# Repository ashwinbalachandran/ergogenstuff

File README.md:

# Summary

Just a repo to save any files related to the ergogen based keyboard I'm trying to build off of https://github.com/tapioki/cephalopoda/tree/main/Architeuthis%20dux

## Notes
The `adux_mod.yml` is not the exact yml that's in the image below, cause of the changes I made in Kicad.

## Changes from the original A.dux
- Changed footprint to `mx`
- Changed the spread and stagger for some columns
- Increased the size of the `raw` outline
- In Kicad
    - repositioned the `promicro` & `trrs` a little bit
    - randomly moved the "empty circles" to edges of the pcb
    - slightly changed the edges of the pcb

## Update - Final
Changes in https://github.com/ashwinbalachandran/ergogenstuff/pull/3

## Issues fixed
https://github.com/ashwinbalachandran/ergogenstuff/issues/1

## Images
Fixed all errors & warning thanks to @duckyb
### Final state

### Broken state - Pre fix?

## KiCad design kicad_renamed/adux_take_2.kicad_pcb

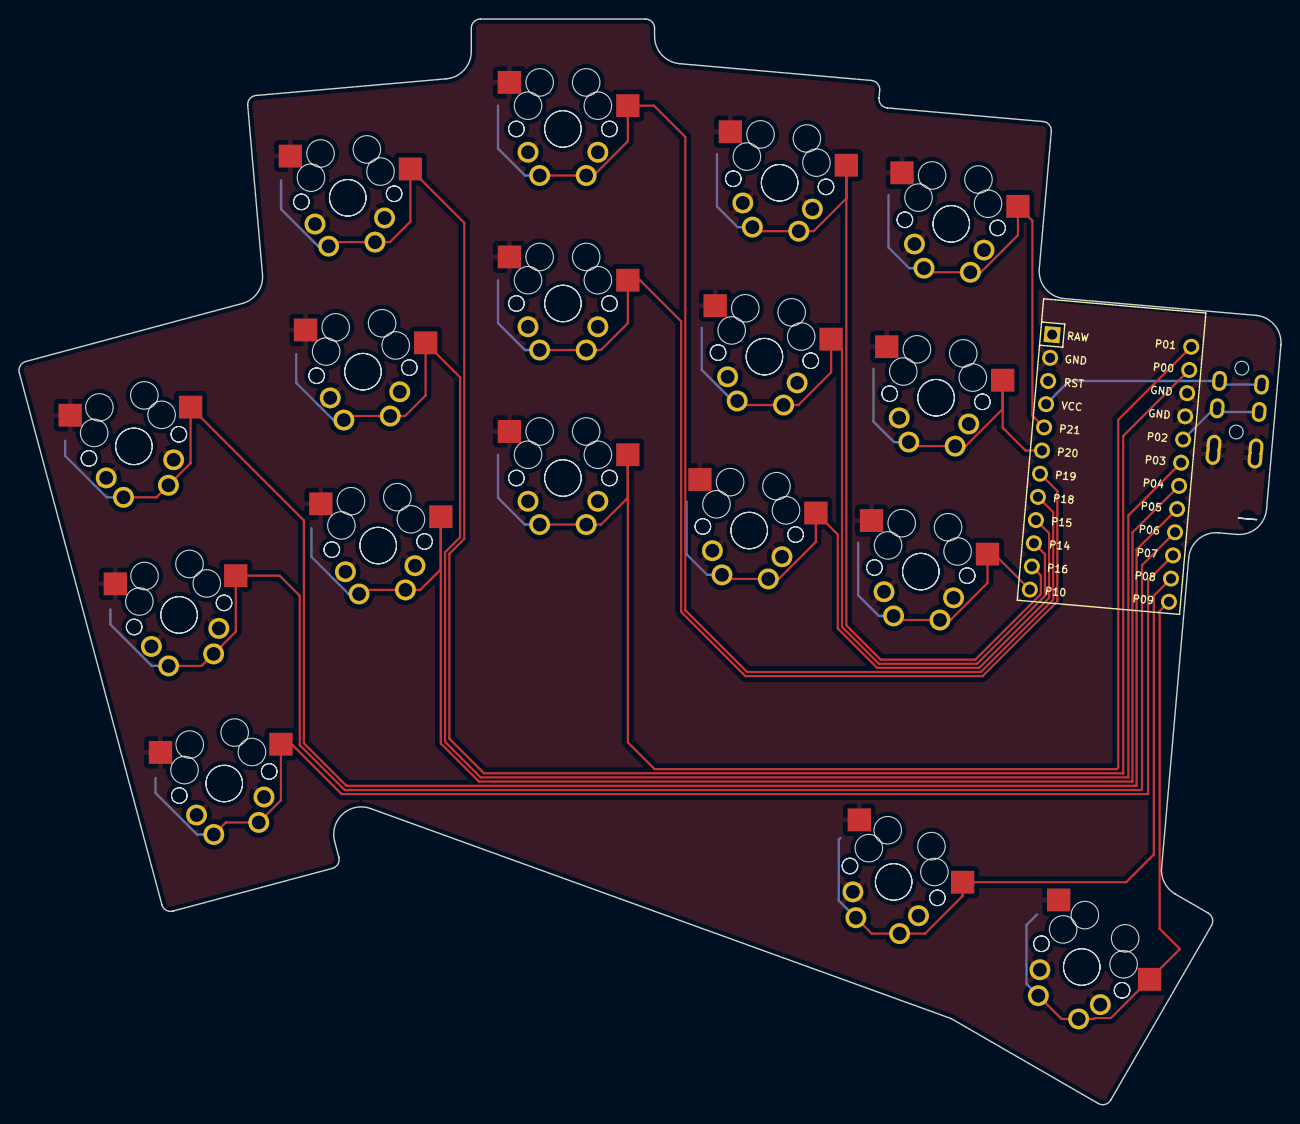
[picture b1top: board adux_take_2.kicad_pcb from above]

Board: 2 copper layers, 137.7 x 118.5 mm, 35 parts (0 on the bottom side), 18 nets.

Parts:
MCU1: ProMicro
S1, S2, S3, S4, S5, S6, S7, S8, S9, S10, S11, S12, S13, S14, S15, S16, S17, S18, S19, S20, S21, S22, S23, S24, S25, S26, S27, S28, S29, S30, S31, S32, S33, S34: MX

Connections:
GND: MCU1.2, MCU1.15, MCU1.16, S1.2, S2.2, S3.2, S4.2, S5.2, S6.2, S7.2, S8.2, S9.2, S10.2, S11.2, S12.2, S13.2, S14.2, S15.2, S16.2, S17.2, S18.2, S19.2, S20.2, S21.2, S22.2, S23.2, S24.2, S25.2, S26.2, S27.2, S28.2, S29.2, S30.2, S31.2, S32.2, S33.2, S34.2
P0: MCU1.14, S11.1, S12.1
P1: MCU1.13, S13.1, S14.1
P3: MCU1.18, S9.1, S10.1
P4: MCU1.19, S7.1, S8.1
P5: MCU1.20, S5.1, S6.1
P6: MCU1.21, S3.1, S4.1
P7: MCU1.22, S1.1, S2.1
P8: MCU1.23, S31.1, S32.1
P9: MCU1.24, S33.1, S34.1
P10: MCU1.12, S25.1, S26.1
P14: MCU1.10, S21.1, S22.1
P15: MCU1.9, S19.1, S20.1
P16: MCU1.11, S23.1, S24.1
P18: MCU1.8, S17.1, S18.1
P19: MCU1.7, S15.1, S16.1
P20: MCU1.6, S27.1, S28.1
P21: MCU1.5, S29.1, S30.1

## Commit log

2022-01-26 Reducing number of keys
2022-03-12 Create adux_mod
2022-05-09 Rename adux_mod to adux_mod.yml
2022-05-09 Adding Kicad files
2022-05-09 Add latest DRC
2022-05-12 Adding fixed pcb & gerbers
2022-05-19 Manually fix pad order, add fill zone for GND
2022-05-19 Adding units and fixing some padding
2022-05-21 Add new folder
2022-05-21 Fresh project with MX spacing
    This reverts the pad order switches back to the ergogen default
2022-05-25 Updated gerbers with spaced trrs jack
2022-05-25 Updated pcb and project files
    Part of the trrs jack change
2022-05-25 Adding gerbers zip
2022-05-25 Updating README.md
2022-07-03 rfpwzxdvkgqwfpbjneio/
